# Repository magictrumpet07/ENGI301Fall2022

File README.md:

# ENGI301Fall2022
<h1> ENGI301 </h1>
Repository for ENGI301 course work

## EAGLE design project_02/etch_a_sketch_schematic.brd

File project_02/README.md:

ENGI 301 Project 2: Etch-a-sketch
-----------------------------------------------------------------------------
This project is a PCB design for an etch-a-sketch drawing device. This design is based on a PocketBeagle microcomputer and uses an SPI Display Screen, two potentiometers, two  buttons, three LEDs (red, green, and blue), and a USB expansion port. Please see the "etch_a_sketch_schematic.brd" for the EAGLE board design, "ENGI301_project_02.pptx" for the mechanical drawing, and "combo_lock2.lbr" for the library file.

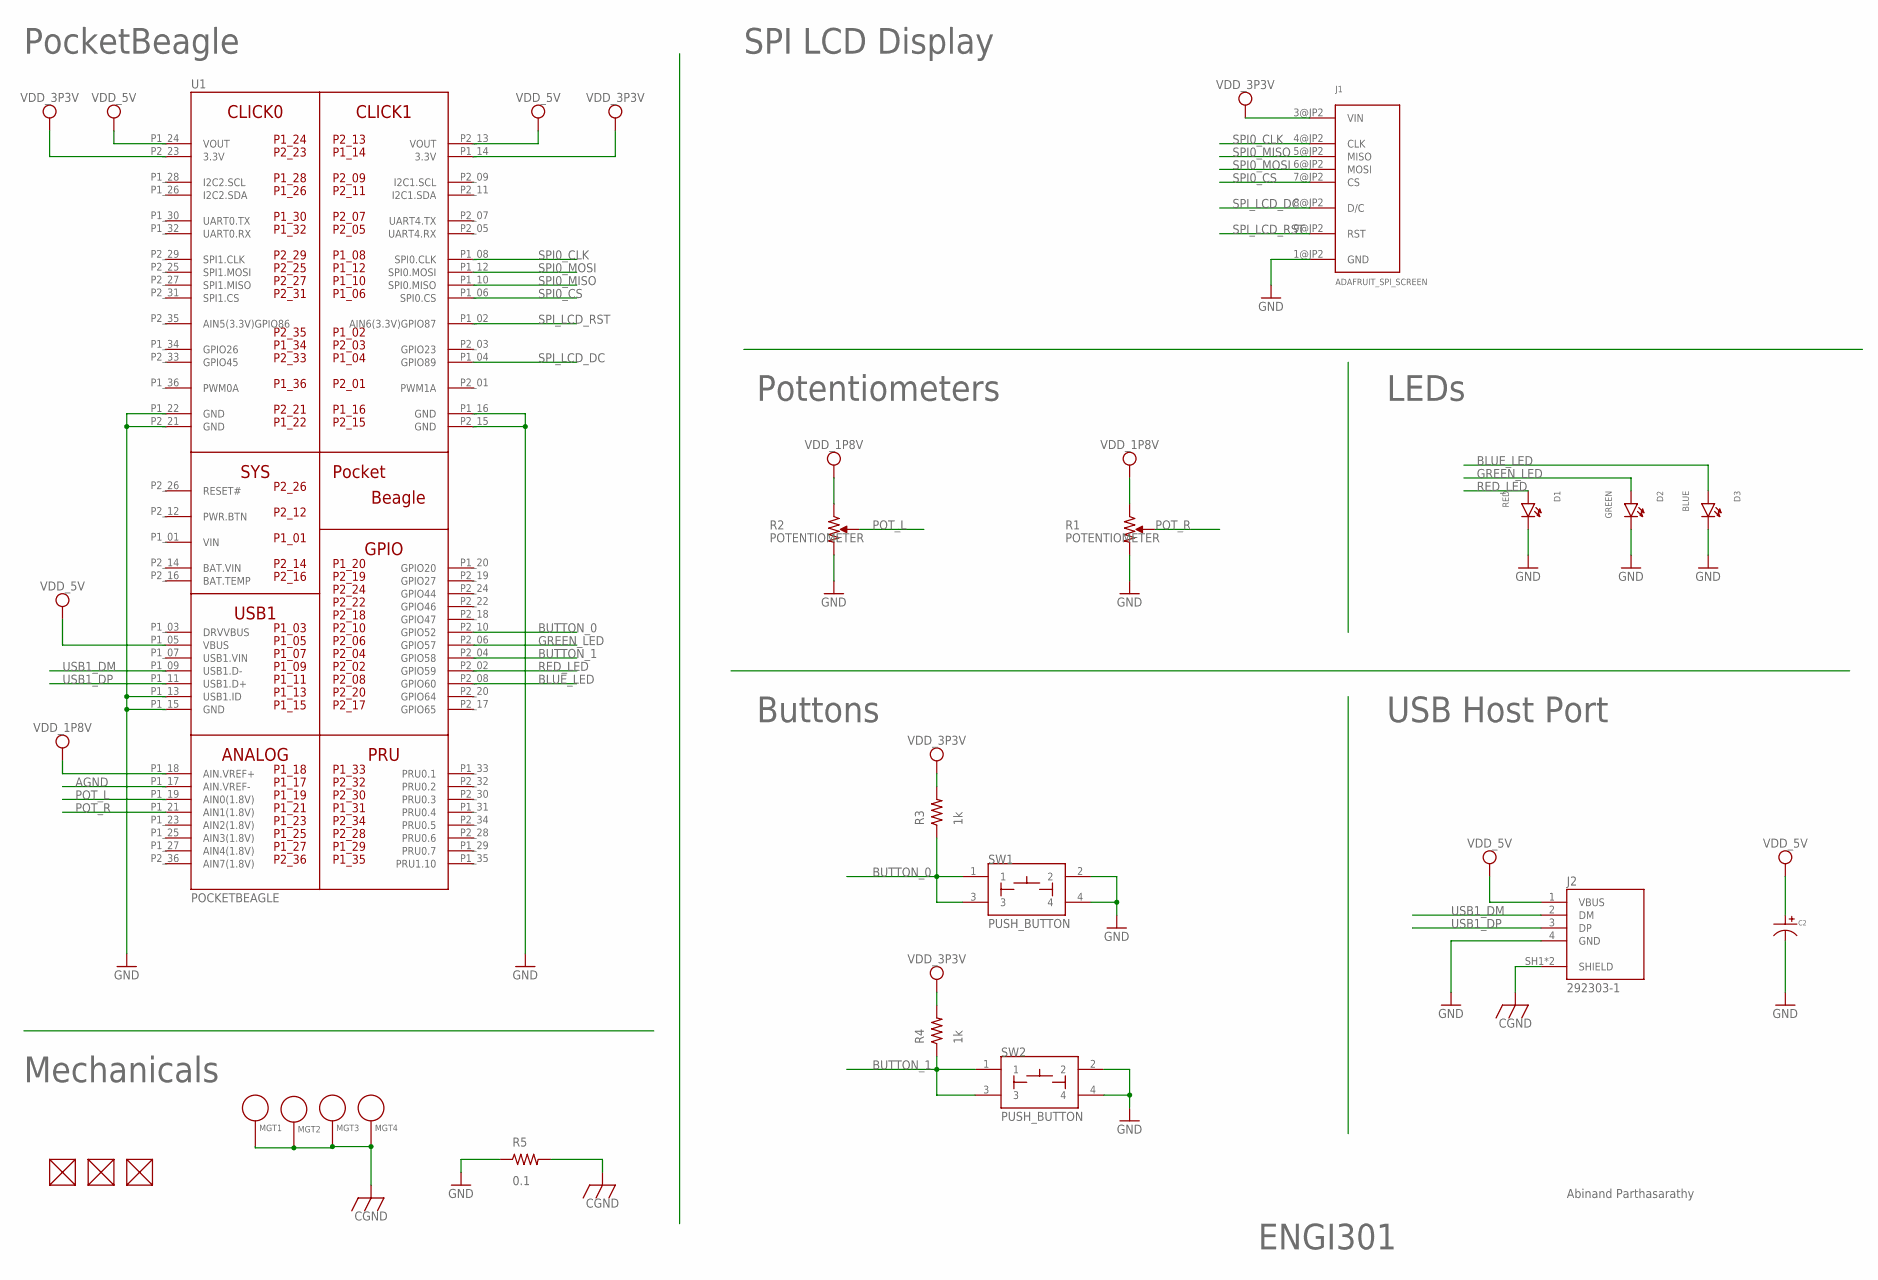
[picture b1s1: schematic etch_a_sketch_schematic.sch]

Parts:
C2: CAPACITOR_P_10MM; CP10MM
D1: RED; EIA-STD
D2: GREEN; EIA-STD
D3: BLUE; EIA-STD
FUD2, FUD4, FUD6: FIDUCIAL; FIDUCIAL_40MIL
J1: ADAFRUIT_SPI_SCREEN; ADAFRUIT_TFT_LCD_PCB
J2: 292303-1; TE_292303-1
MGT1, MGT2, MGT3, MGT4: MOUNTING_HOLE
R1, R2: POTENTIOMETER; POT-PO90S
R3, R4: 1k; R0603
R5: 0.1; R0603
SW1, SW2: PUSH_BUTTON; BUTTON_12.5MM
U1: POCKETBEAGLE

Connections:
AGND: U1.P1_17 (AIN.VREF-)
BAT.VIN: U1.P2_14 (BAT.VIN)
BLUE_LED: D3.ANODE, U1.P2_08 (GPIO60)
BUTTON_0: R3.1, SW1.1, SW1.3, U1.P2_10 (GPIO52)
BUTTON_1: R4.1, SW2.1, SW2.3, U1.P2_04 (GPIO58)
CGND: J2.SH1 (SHIELD), J2.SH2 (SHIELD), MGT1.P$1, MGT2.P$1, MGT3.P$1, MGT4.P$1, R5.2
GND: C2.P$2, D1.CATHODE, D2.CATHODE, D3.CATHODE, J1.1@JP2 (GND), J2.4 (GND), R1.CW, R2.CW, R5.1, SW1.2, SW1.4, SW2.2, SW2.4, U1.P1_13 (USB1.ID), U1.P1_15 (GND), U1.P1_16 (GND), U1.P1_22 (GND), U1.P2_15 (GND), U1.P2_21 (GND)
GREEN_LED: D2.ANODE, U1.P2_06 (GPIO57)
POT_L: R2.S, U1.P1_19 (AIN0(1.8V))
POT_R: R1.S, U1.P1_21 (AIN1(1.8V))
RED_LED: D1.ANODE, U1.P2_02 (GPIO59)
SPI0_CLK: J1.4@JP2 (CLK), U1.P1_08 (SPI0.CLK)
SPI0_CS: J1.7@JP2 (CS), U1.P1_06 (SPI0.CS)
SPI0_MISO: J1.5@JP2 (MISO), U1.P1_10 (SPI0.MISO)
SPI0_MOSI: J1.6@JP2 (MOSI), U1.P1_12 (SPI0.MOSI)
SPI_LCD_DC: J1.8@JP2 (D/C), U1.P1_04 (GPIO89)
SPI_LCD_RST: J1.9@JP2 (RST), U1.P1_02 (AIN6(3.3V)GPIO87)
USB1_DM: J2.2 (DM), U1.P1_09 (USB1.D-)
USB1_DP: J2.3 (DP), U1.P1_11 (USB1.D+)
VDD_1P8V: R1.CCW, R2.CCW, U1.P1_18 (AIN.VREF+)
VDD_3P3V: J1.3@JP2 (VIN), R3.2, R4.2, U1.P1_14 (3.3V), U1.P2_23 (3.3V)
VDD_5V: C2.P$1, J2.1 (VBUS), U1.P1_05 (VBUS), U1.P1_24 (VOUT), U1.P2_13 (VOUT)
VIN: U1.P1_01 (VIN)

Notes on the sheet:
PocketBeagle
Mechanicals
SPI LCD Display
LEDs
Potentiometers
Buttons
USB Host Port
ENGI301
Abinand Parthasarathy

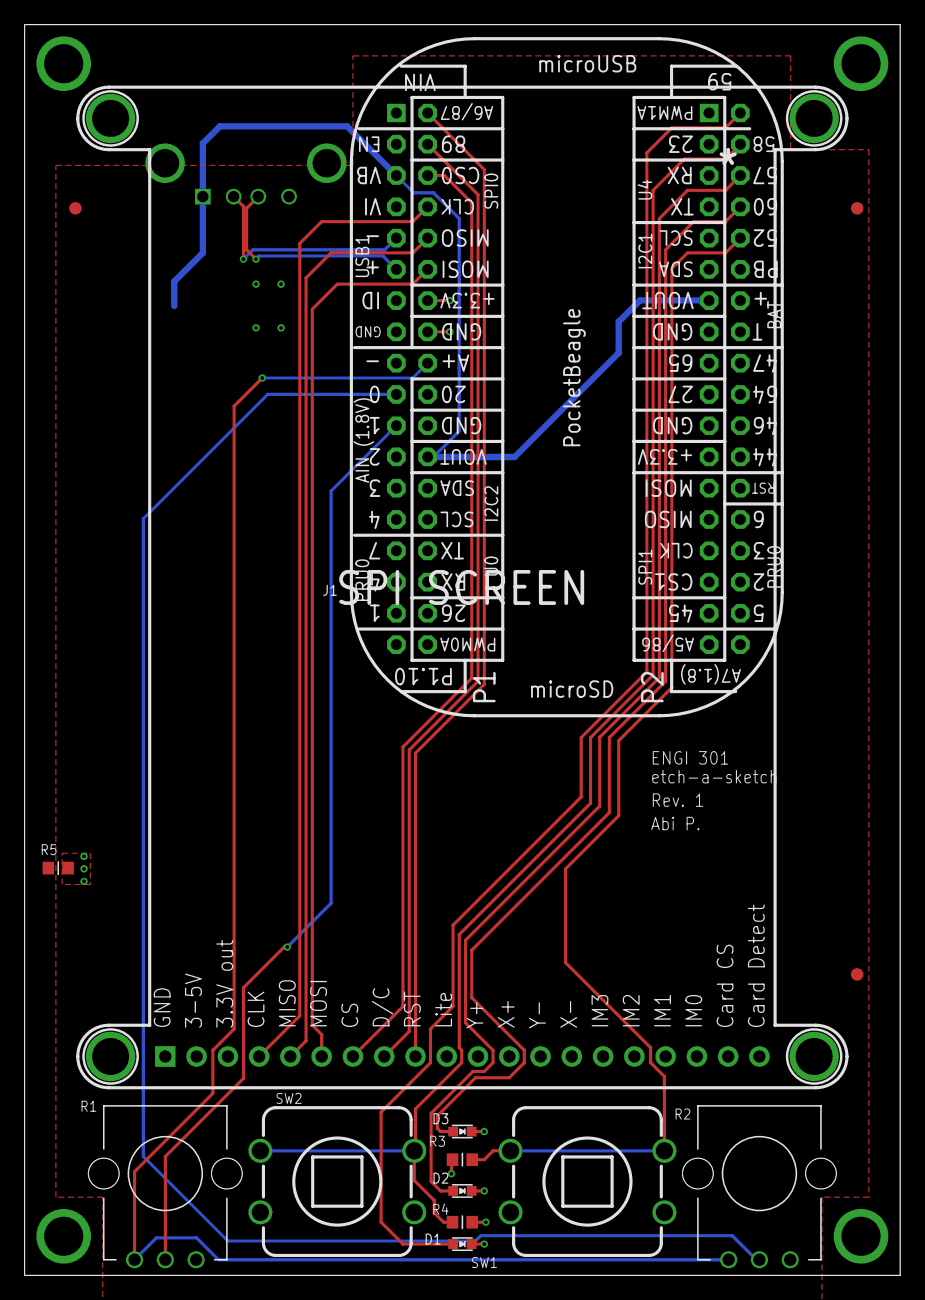
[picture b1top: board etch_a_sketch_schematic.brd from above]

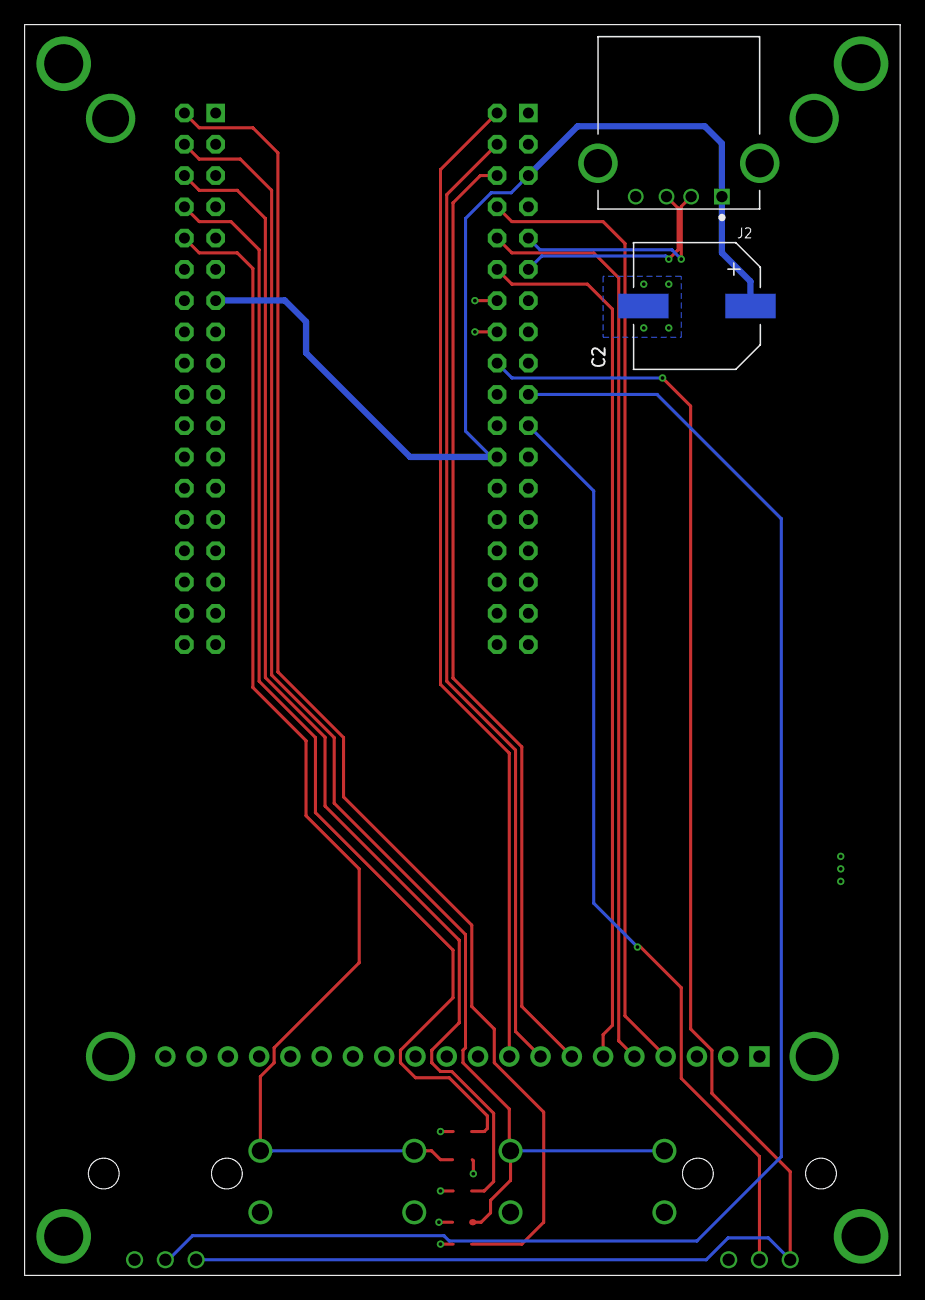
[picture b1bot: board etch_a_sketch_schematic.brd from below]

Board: 4 copper layers, 71.1 x 101.6 mm, 21 parts (2 on the bottom side), 20 nets.

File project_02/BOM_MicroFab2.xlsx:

Designator | Value | Footprint | Populate | MPN | Manufacturer
C2 |  | CP10MM | 1 | MF-CAP-10MM-220uF | MacroFab
D1 | RED | EIA-STD | 1 | MF-LED-0603-RED | MacroFab
D2 | GREEN | EIA-STD | 1 | MF-LED-0603-GREEN | MacroFab
D3 | BLUE | EIA-STD | 1 | SMLE12BC7TT86 | ROHM
FUD2 | FIDUCIAL | FIDUCIAL_40MIL | 0
FUD4 | FIDUCIAL | FIDUCIAL_40MIL | 0
FUD6 | FIDUCIAL | FIDUCIAL_40MIL | 0
J1 | ADAFRUIT_SPI_SCREEN | ADAFRUIT_TFT_LCD_PCB | 0
J2 | 292303-1 | TE_292303-1 | 1 | 292303-1 | TE Connectivity
MGT1 | MOUNTING_HOLE | MOUNTING_HOLE | 0
MGT2 | MOUNTING_HOLE | MOUNTING_HOLE | 0
MGT3 | MOUNTING_HOLE | MOUNTING_HOLE | 0
MGT4 | MOUNTING_HOLE | MOUNTING_HOLE | 0
R1 | POTENTIOMETER | POT-PO90S | 1 | MF-RES-TC33X-10K | MacroFab
R2 | POTENTIOMETER | POT-PO90S | 1 | MF-RES-TC33X-10K | MacroFab
R3 | 1k | R0603 | 1 | MF-RES-0603-1K | MacroFab
R4 | 1k | R0603 | 1 | MF-RES-0603-1K | MacroFab
R5 | 0.1 | R0603 | 1 | 0603B104K500CT | Walsin Technologies
SW1 | PUSH_BUTTON | BUTTON_12.5MM | 0 | ADAPTERFPUSHBUTTON | C&K Components
SW2 | PUSH_BUTTON | BUTTON_12.5MM | 0 | ADAPTERFPUSHBUTTON | C&K Components
U1 | POCKETBEAGLE | POCKETBEAGLE | 0 | POCKETBEAGLE | BeagleBoard

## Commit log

2022-09-27 original simple calc
2022-09-27 Simple Calc for HW4
2022-11-22 adding dc motor
2022-11-22 updating dc motor
2022-12-14 Create DealerBot Code
2022-12-14 Create tempfile
